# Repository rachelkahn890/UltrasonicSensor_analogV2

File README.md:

# UltrasonicSensor_analog
Just the analog part of an ultrasonic sensor.

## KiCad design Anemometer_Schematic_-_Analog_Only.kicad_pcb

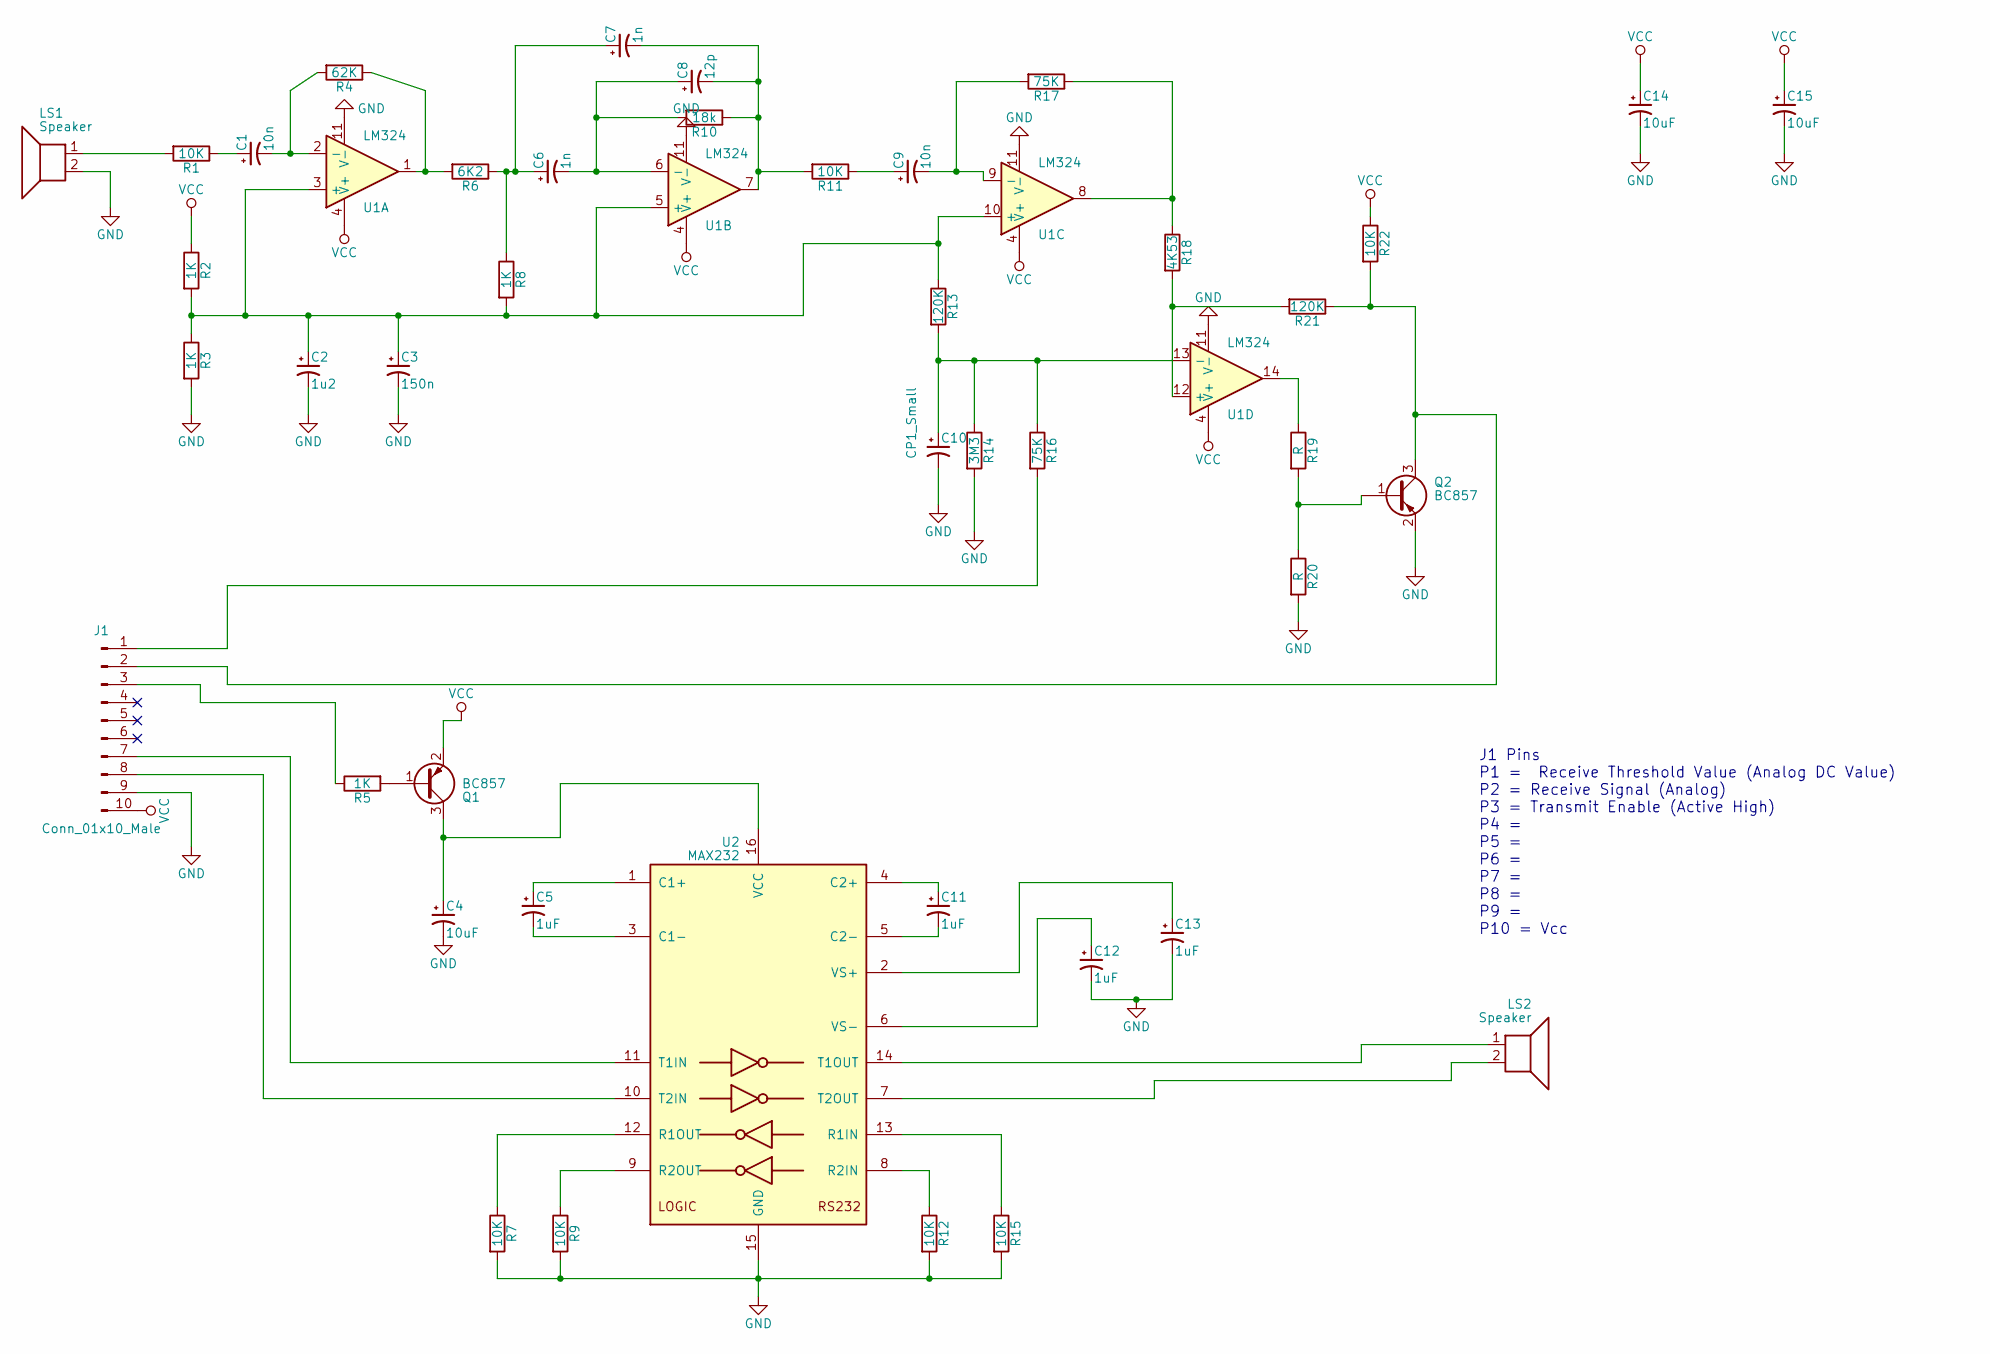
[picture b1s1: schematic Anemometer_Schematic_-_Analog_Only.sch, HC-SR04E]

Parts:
C1, C9: 10n; C_0603_HandSoldering
C2: 1u2; C_0603_HandSoldering
C3: 150n; C_0603_HandSoldering
C4, C14, C15: 10uF; C_0603_HandSoldering
C5, C11, C12, C13: 1uF; C_0603_HandSoldering
C6, C7: 1n; C_0603_HandSoldering
C8: 12p; C_0603_HandSoldering
C10: CP1_Small; C_0603_HandSoldering
J1: Conn_01x10_Male; Socket_Strip_Straight_1x10_Pitch2.54mm
LS1, LS2: Speaker; ultrasonic_speaker
Q1, Q2: BC857; SOT-23
R1, R7, R9, R11, R12, R15, R22: 10K; R_0603_HandSoldering
R2, R3, R5, R8: 1K; R_0603_HandSoldering
R4: 62K; R_0603_HandSoldering
R6: 6K2; R_0603_HandSoldering
R10: 18k; R_0603_HandSoldering
R13, R21: 120K; R_0603_HandSoldering
R14: 3M3; R_0603_HandSoldering
R16, R17: 75K; R_0603_HandSoldering
R18: 4K53; R_0603_HandSoldering
R19, R20: R; R_0603_HandSoldering
U1: LM324
U2: MAX232; MAX232A

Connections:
GND: C2.2, C3.2, C4.2, C10.2, C12.2, C13.2, C14.2, C15.2, J1.9, LS1.2, Q2.2 (E), R3.2, R7.2, R9.2, R12.2, R14.2, R15.2, R20.2, U1.11 (V-), U2.15 (GND)
unnamed: C1.1, R1.1
unnamed: C1.2, R4.2, U1.2 (-)
unnamed: C2.1, C3.1, R2.2, R3.1, R8.2, R13.1, U1.3 (+), U1.5 (+), U1.10 (+)
unnamed: C4.1, Q1.3 (C), U2.16 (VCC)
unnamed: C5.1, U2.1 (C1+)
unnamed: C5.2, U2.3 (C1-)
unnamed: C6.1, C7.1, R6.1, R8.1
unnamed: C6.2, C8.1, R10.2, U1.6 (-)
unnamed: C7.2, C8.2, R10.1, R11.2, U1.7
unnamed: C9.1, R11.1
unnamed: C9.2, R17.2, U1.9 (-)
unnamed: C10.1, R13.2, R14.1, R16.1, U1.13 (-)
unnamed: C11.1, U2.4 (C2+)
unnamed: C11.2, U2.5 (C2-)
unnamed: C12.1, U2.6 (VS-)
unnamed: C13.1, U2.2 (VS+)
unnamed: J1.1, R16.2
unnamed: J1.2, Q2.3 (C), R21.1, R22.2
unnamed: J1.3, R5.1
unnamed: J1.7, U2.11 (T1IN)
unnamed: J1.8, U2.10 (T2IN)
unnamed: LS1.1, R1.2
unnamed: LS2.1, U2.14 (T1OUT)
unnamed: LS2.2, U2.7 (T2OUT)
unnamed: Q1.1 (B), R5.2
unnamed: Q2.1 (B), R19.2, R20.1
unnamed: R4.1, R6.2, U1.1
unnamed: R7.1, U2.12 (R1OUT)
unnamed: R9.1, U2.9 (R2OUT)
unnamed: R12.1, U2.8 (R2IN)
unnamed: R15.1, U2.13 (R1IN)
unnamed: R17.1, R18.1, U1.8
unnamed: R18.2, R21.2, U1.12 (+)
unnamed: R19.1, U1.14
VCC: C14.1, C15.1, J1.10, Q1.2 (E), R2.1, R22.1, U1.4 (V+)

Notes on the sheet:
J1 Pins P1 = Receive Threshold Value (Analog DC Value) P2 = Receive Signal (Analog) P3 = Transmit Enable (Active High) P4 = P5 = P6 = P7 = P8 = P9 = P10 = Vcc

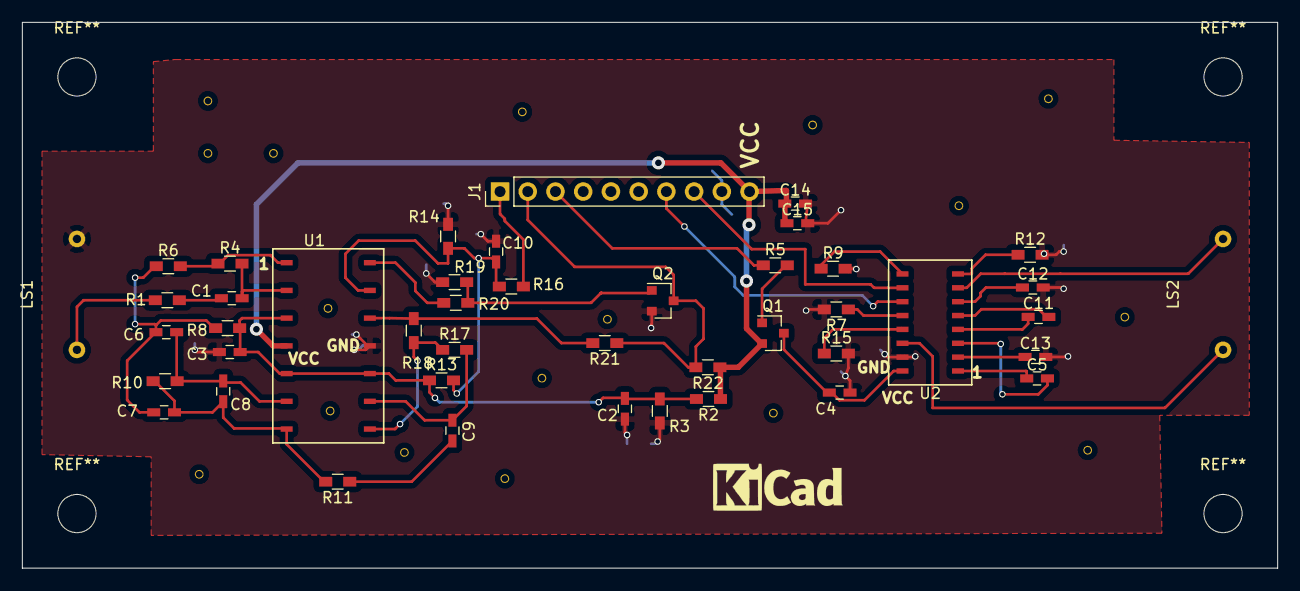
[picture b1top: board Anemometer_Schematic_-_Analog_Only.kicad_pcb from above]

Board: 2 copper layers, 115.0 x 50.0 mm, 44 parts (0 on the bottom side), 36 nets.

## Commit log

2018-02-10 :octocat: Added .gitattributes & .gitignore files
2018-02-12 tweaked layour
    Added a ground pour on the top layer with via's to tie top and bottom behind.
    moved some components to clean up routing.
2018-02-19 Add Gerber files and drill file
